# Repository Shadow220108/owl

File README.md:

<h1 align="center">
<br>
Owl
<br>
</h1>

<h3 align="center">

A compact STM32F072 dev board with USB-C :D

</h3>

<div align="center">

</div>

Owl is my own STM32 dev board, kinda like a blue pill but with USB-C and made by me. It uses the STM32F072CBT6 which has native USB, so you can plug it in and flash it over USB using the built in bootloader, no programmer needed. Every usable pin goes out to the two long headers on the sides.

The PCB is 4 layers, 72 x 30.48 mm, black with gold pads, and it has some art on the back cause a plain back is boring.

## Features

* STM32F072CBT6, 48 MHz Cortex-M0, 128kb flash, native USB
* USB-C with 5.1k CC resistors, USBLC6 ESD protection and a 500mA fuse
* AMS1117 3.3V regulator
* 8 MHz crystal
* Reset and BOOT0 buttons, hold BOOT0 and press reset to get into the USB bootloader
* Blue user LED on PA5 and a green power LED
* 10 pin Cortex debug header and a 5 pin 2.54mm SWD header for cheap ST-Link clones
* Two 20 pin headers with every PA, PB and PC13-15 pin
* Ground plane on inner 1 and a 3.3V plane on inner 2

PA11 and PA12 are the USB data lines and PA13 / PA14 are SWDIO and SWCLK, so try not to use those for other stuff.

## Schematic

|USB-C|Power|
|-|-|
|||

|Decoupling, crystal, reset and boot|SWD|
|-|-|
|||

## PCB

|Routed|Ground pour|
|-|-|
|||

The STM32 is rotated 45 degrees so the traces fan out to the headers easier. The decoupling caps and crystal sit right next to the chip and there are 99 vias stitching the grounds together.

## Art

The back has "Owl" and "made by Shadow" in cursive with a little line drawing with flowers in the middle.

## Why was it made?

I wanted a dev board that's actually mine, with USB-C and all the pins broken out, instead of buying another blue pill. And designing a 4 layer board around an STM32 seemed like a fun way to learn :D

## BOM

|Item|Qty|Price ($)|Vendor|
|-|-|-|-|
|PCBA (4 layer PCB + assembly)|1|43.60|JLCPCB|
|Shipping|1|8.19|JLCPCB|
|Total||51.79||

Here is the full LCSC BOM of individual parts generated from KiCAD 

|Designator         |Footprint                                              |Quantity|Value                      |LCSC Part #|Part Name                                    |Unit Price (USD)|Ext Price (USD)|Price Tier|
|-------------------|-------------------------------------------------------|--------|---------------------------|-----------|---------------------------------------------|----------------|---------------|----------|
|C1                 |0805                                                   |1       |10uF                       |C15850     |Samsung CL21A106KAYNNNE                      |0.0856          |0.0856         |20+       |
|C10                |0603                                                   |1       |1uF                        |C15849     |Samsung CL10A105KB8NNNC                      |0.0056          |0.0056         |50+       |
|C11                |0603                                                   |1       |10nF                       |C57112     |Fenghua 0603B103K500NT                       |0.0116          |0.0116         |50+       |
|C12, C13           |0603                                                   |2       |10pF                       |C1634      |Samsung CL10C100JB8NNNC                      |0.0059          |0.0118         |100+      |
|C14, C4, C5, C6, C8|0603                                                   |5       |100nF                      |C14663     |Yageo CC0603KRX7R9BB104                      |0.0025          |0.0125         |1+        |
|C2                 |CP_EIA-3528-21_Kemet-B                                 |1       |22uF Tant.                 |C8020      |Kyocera AVX TAJB226K016RNJ                   |0.1988          |0.1988         |1+        |
|C7, C9             |0805                                                   |2       |4.7uF                      |C1779      |Samsung CL21A475KAQNNNE                      |0.0147          |0.0294         |20+       |
|D1                 |0603                                                   |1       |Green                      |C72043     |Everlight 19-217/GHC-YR1S2/3T                |0.0309          |0.0309         |20+       |
|D2                 |0603                                                   |1       |Blue                       |C72041     |Everlight 19-217/BHC-ZL1M2RY/3T              |0.0172          |0.0172         |20+       |
|F1                 |1206                                                   |1       |500mA                      |C883122    |BHFUSE BSMD1206-050-6V (PTC resettable)      |0.0453          |0.0453         |10+       |
|FB1                |0603                                                   |1       |600R@100MHz                |C1002      |Sunlord GZ1608D601TF                         |0.0047          |0.0047         |20+       |
|J1                 |USB_C_Receptacle_GCT_USB4105-xx-A_16P_TopMnt_Horizontal|1       |USB_C_Receptacle_USB2.0_16P|C3020560   |GCT USB4105-GF-A                             |1.2075          |1.2075         |1+        |
|J2                 |PinHeader_2x05_P1.27mm_Vertical_SMD                    |1       |Cortex Debug 10-pin        |C3975188   |HCTL PZ127-2-05-S                            |0.1456          |0.1456         |5+        |
|J3                 |PinHeader_1x20_P2.54mm_Vertical                        |1       |Header PA                  |C50981     |BOOMELE 2.54-1*20P pin header                |0.0999          |0.0999         |5+        |
|J4                 |PinHeader_1x20_P2.54mm_Vertical                        |1       |Header PB/PC               |C50981     |BOOMELE 2.54-1*20P pin header                |0.0999          |0.0999         |5+        |
|J5                 |PinHeader_1x05_P2.54mm_Vertical                        |1       |SWD 2.54mm                 |C50981     |BOOMELE 2.54-1*20P pin header (cut to 5 pins)|0.0999          |0.0999         |5+        |
|R1, R2             |0603                                                   |2       |5.1k                       |C23186     |UNI-ROYAL 0603WAF5101T5E                     |0.0012          |0.0024         |100+      |
|R3, R4             |0603                                                   |2       |1k                         |C21190     |UNI-ROYAL 0603WAF1001T5E                     |0.0010          |0.0020         |100+      |
|R5                 |0603                                                   |1       |10k                        |C25804     |UNI-ROYAL 0603WAF1002T5E                     |0.0010          |0.0010         |100+      |
|SW1                |SW_SPST_TL3342                                         |1       |RESET                      |C2886898   |E-Switch TL3342F160QG                        |0.6625          |0.6625         |1+        |
|SW2                |SW_SPST_TL3342                                         |1       |BOOT0                      |C2886898   |E-Switch TL3342F160QG                        |0.6625          |0.6625         |1+        |
|U1                 |LQFP-48_7x7mm_P0.5mm                                   |1       |STM32F072CBTx              |C81720     |STMicroelectronics STM32F072CBT6             |1.3444          |1.3444         |1+        |
|U2                 |SOT-23-6                                               |1       |USBLC6-2SC6                |C7519      |STMicroelectronics USBLC6-2SC6               |0.1116          |0.1116         |5+        |
|U3                 |SOT-223-3_TabPin2                                      |1       |AMS1117-3.3                |C6186      |Advanced Monolithic Systems AMS1117-3.3      |0.2259          |0.2259         |5+        |
|Y1                 |Crystal_SMD_3225-4Pin_3.2x2.5mm                        |1       |8MHz CL=10pF               |C518154    |Suzhou Liming 3225-8.00-10-10-10/A           |0.2480          |0.2480         |5+        |

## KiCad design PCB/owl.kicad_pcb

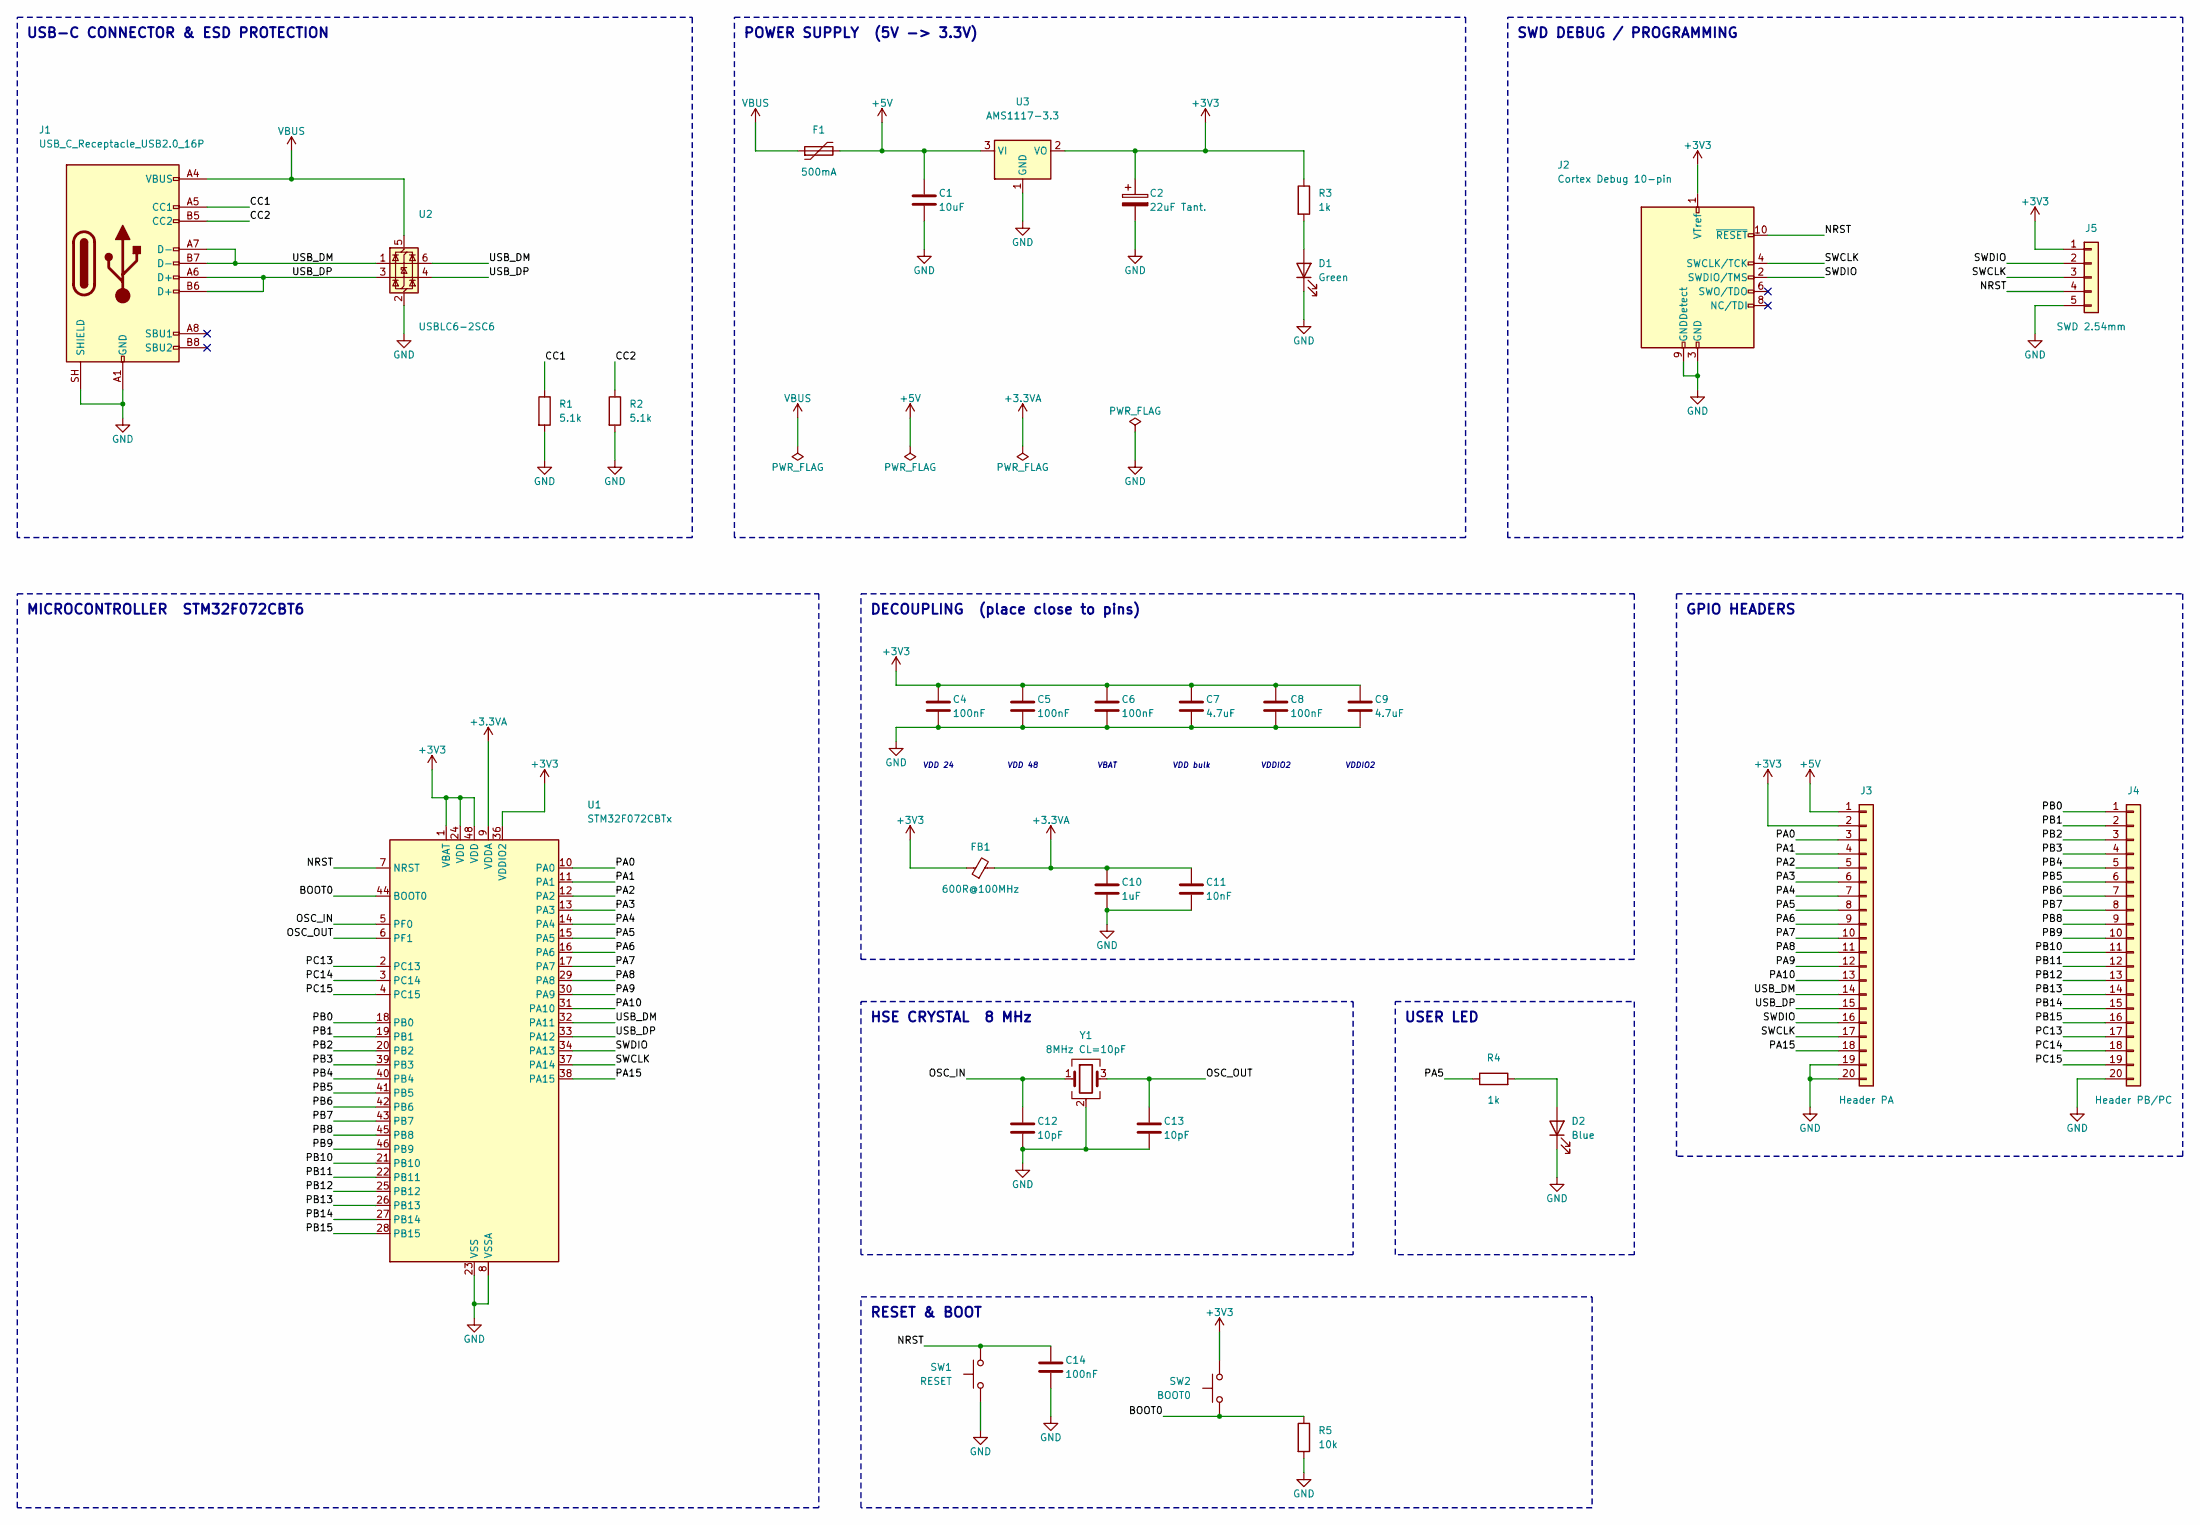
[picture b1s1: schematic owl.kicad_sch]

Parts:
C1: 10uF; C_0805_2012Metric
C2: 22uF Tant.; CP_EIA-3528-21_Kemet-B
C4, C5, C6, C8, C14: 100nF; C_0603_1608Metric
C7, C9: 4.7uF; C_0805_2012Metric
C10: 1uF; C_0603_1608Metric
C11: 10nF; C_0603_1608Metric
C12, C13: 10pF; C_0603_1608Metric
D1: Green; LED_0603_1608Metric
D2: Blue; LED_0603_1608Metric
F1: 500mA; Fuse_1206_3216Metric
FB1: 600R@100MHz; L_0603_1608Metric
J1: USB_C_Receptacle_USB2.0_16P; USB_C_Receptacle_GCT_USB4105-xx-A_16P_TopMnt_Horizontal
J2: Cortex Debug 10-pin; PinHeader_2x05_P1.27mm_Vertical_SMD
J3: Header PA; PinHeader_1x20_P2.54mm_Vertical
J4: Header PB/PC; PinHeader_1x20_P2.54mm_Vertical
J5: SWD 2.54mm; PinHeader_1x05_P2.54mm_Vertical
R1, R2: 5.1k; R_0603_1608Metric
R3, R4: 1k; R_0603_1608Metric
R5: 10k; R_0603_1608Metric
SW1: RESET; SW_SPST_TL3342
SW2: BOOT0; SW_SPST_TL3342
U1: STM32F072CBTx; LQFP-48_7x7mm_P0.5mm
U2: USBLC6-2SC6; SOT-23-6
U3: AMS1117-3.3; SOT-223-3_TabPin2
Y1: 8MHz CL=10pF; Crystal_SMD_3225-4Pin_3.2x2.5mm

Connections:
+3.3VA: C10.1, C11.1, FB1.2, U1.9 (VDDA)
+3V3: C2.1, C4.1, C5.1, C6.1, C7.1, C8.1, C9.1, FB1.1, J2.1 (VTref), J3.2, J5.1, R3.1, SW2.2, U1.1 (VBAT), U1.24 (VDD), U1.36 (VDDIO2), U1.48 (VDD), U3.2 (VO)
+5V: C1.1, F1.2, J3.1, U3.3 (VI)
/BOOT0: R5.1, SW2.1, U1.44 (BOOT0)
/CC1: J1.A5 (CC1), R1.1
/CC2: J1.B5 (CC2), R2.1
/NRST: C14.1, J2.10 (~RESET), J5.4, SW1.2, U1.7 (NRST)
/OSC_IN: C12.1, U1.5 (PF0), Y1.1
/OSC_OUT: C13.1, U1.6 (PF1), Y1.3
/PA0: J3.3, U1.10 (PA0)
/PA1: J3.4, U1.11 (PA1)
/PA2: J3.5, U1.12 (PA2)
/PA3: J3.6, U1.13 (PA3)
/PA4: J3.7, U1.14 (PA4)
/PA5: J3.8, R4.1, U1.15 (PA5)
/PA6: J3.9, U1.16 (PA6)
/PA7: J3.10, U1.17 (PA7)
/PA8: J3.11, U1.29 (PA8)
/PA9: J3.12, U1.30 (PA9)
/PA10: J3.13, U1.31 (PA10)
/PA15: J3.18, U1.38 (PA15)
/PB0: J4.1, U1.18 (PB0)
/PB1: J4.2, U1.19 (PB1)
/PB2: J4.3, U1.20 (PB2)
/PB3: J4.4, U1.39 (PB3)
/PB4: J4.5, U1.40 (PB4)
/PB5: J4.6, U1.41 (PB5)
/PB6: J4.7, U1.42 (PB6)
/PB7: J4.8, U1.43 (PB7)
/PB8: J4.9, U1.45 (PB8)
/PB9: J4.10, U1.46 (PB9)
/PB10: J4.11, U1.21 (PB10)
/PB11: J4.12, U1.22 (PB11)
/PB12: J4.13, U1.25 (PB12)
/PB13: J4.14, U1.26 (PB13)
/PB14: J4.15, U1.27 (PB14)
/PB15: J4.16, U1.28 (PB15)
/PC13: J4.17, U1.2 (PC13)
/PC14: J4.18, U1.3 (PC14)
/PC15: J4.19, U1.4 (PC15)
/SWCLK: J2.4 (SWCLK/TCK), J3.17, J5.3, U1.37 (PA14)
/SWDIO: J2.2 (SWDIO/TMS), J3.16, J5.2, U1.34 (PA13)
/USB_DM: J1.A7 (D-), J1.B7 (D-), J3.14, U1.32 (PA11), U2.1 (I/O1), U2.6 (I/O1)
/USB_DP: J1.A6 (D+), J1.B6 (D+), J3.15, U1.33 (PA12), U2.3 (I/O2), U2.4 (I/O2)
GND: C1.2, C2.2, C4.2, C5.2, C6.2, C7.2, C8.2, C9.2, C10.2, C11.2, C12.2, C13.2, C14.2, D1.1 (K), D2.1 (K), J1.A1 (GND), J1.A12 (GND), J1.B1 (GND), J1.B12 (GND), J1.SH (SHIELD), J2.3 (GND), J2.5 (GND), J2.9 (GNDDetect), J3.19, J3.20, J4.20, J5.5, R1.2, R2.2, R5.2, SW1.1, U1.8 (VSSA), U1.23 (VSS), U1.35 (VSS), U1.47 (VSS), U2.2 (GND), U3.1 (GND), Y1.2 (G), Y1.4 (G)
unnamed: D1.2 (A), R3.2
unnamed: D2.2 (A), R4.2
VBUS: F1.1, J1.A4 (VBUS), J1.A9 (VBUS), J1.B4 (VBUS), J1.B9 (VBUS), U2.5 (VBUS)

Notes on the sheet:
HSE CRYSTAL 8 MHz
VBAT
RESET & BOOT
USB-C CONNECTOR & ESD PROTECTION
VDD 24
DECOUPLING (place close to pins)
MICROCONTROLLER STM32F072CBT6
POWER SUPPLY (5V -> 3.3V)
GPIO HEADERS
VDD bulk
SWD DEBUG / PROGRAMMING
VDDIO2
VDD 48
USER LED

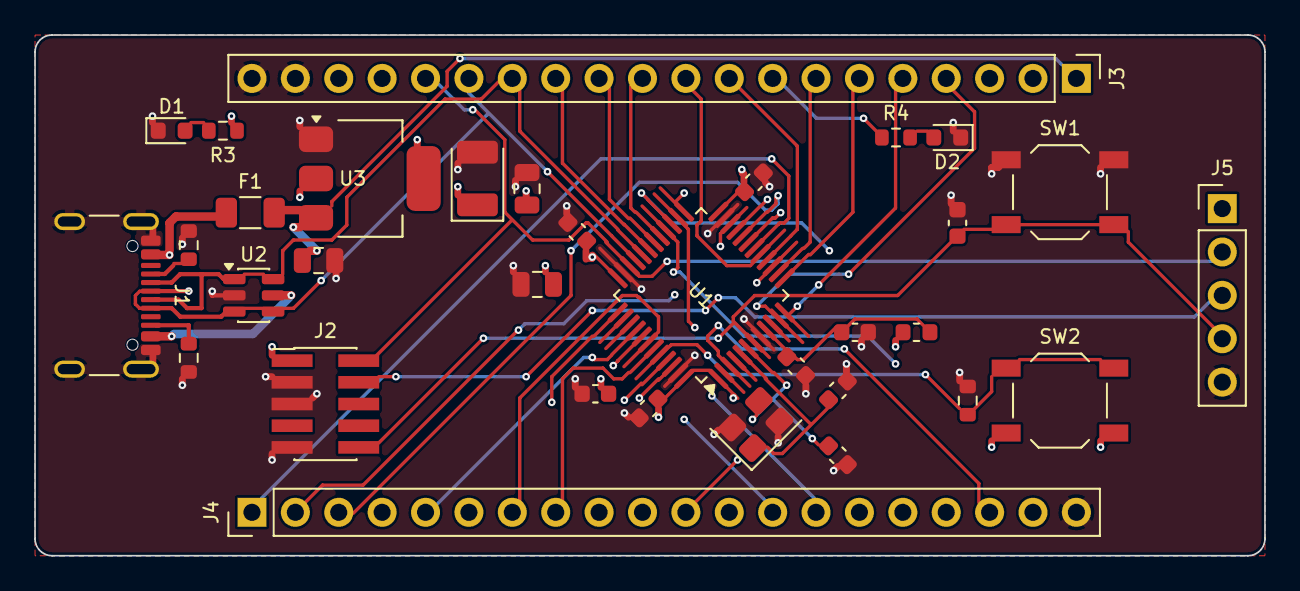
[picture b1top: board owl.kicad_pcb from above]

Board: 4 copper layers, 72.0 x 30.5 mm, 33 parts (0 on the bottom side), 48 nets.

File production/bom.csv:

Designator,Footprint,Quantity,Value,LCSC Part #
C1,0805,1,10uF,
C10,0603,1,1uF,
C11,0603,1,10nF,
"C12, C13",0603,2,10pF,
"C14, C4, C5, C6, C8",0603,5,100nF,
C2,CP_EIA-3528-21_Kemet-B,1,22uF Tant.,
"C7, C9",0805,2,4.7uF,
D1,0603,1,Green,
D2,0603,1,Blue,
F1,1206,1,500mA,
FB1,0603,1,600R@100MHz,
J1,USB_C_Receptacle_GCT_USB4105-xx-A_16P_TopMnt_Horizontal,1,USB_C_Receptacle_USB2.0_16P,
J2,PinHeader_2x05_P1.27mm_Vertical_SMD,1,Cortex Debug 10-pin,
J3,PinHeader_1x20_P2.54mm_Vertical,1,Header PA,
J4,PinHeader_1x20_P2.54mm_Vertical,1,Header PB/PC,
J5,PinHeader_1x05_P2.54mm_Vertical,1,SWD 2.54mm,
"R1, R2",0603,2,5.1k,
"R3, R4",0603,2,1k,
R5,0603,1,10k,
SW1,SW_SPST_TL3342,1,RESET,
SW2,SW_SPST_TL3342,1,BOOT0,
U1,LQFP-48_7x7mm_P0.5mm,1,STM32F072CBTx,
U2,SOT-23-6,1,USBLC6-2SC6,
U3,SOT-223-3_TabPin2,1,AMS1117-3.3,
Y1,Crystal_SMD_3225-4Pin_3.2x2.5mm,1,8MHz CL=10pF,
